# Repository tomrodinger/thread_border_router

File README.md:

# thread_border_router
This is an implementation of a low cost Matter / Thread Border Router to bridge from Ethernet to 802.15.4

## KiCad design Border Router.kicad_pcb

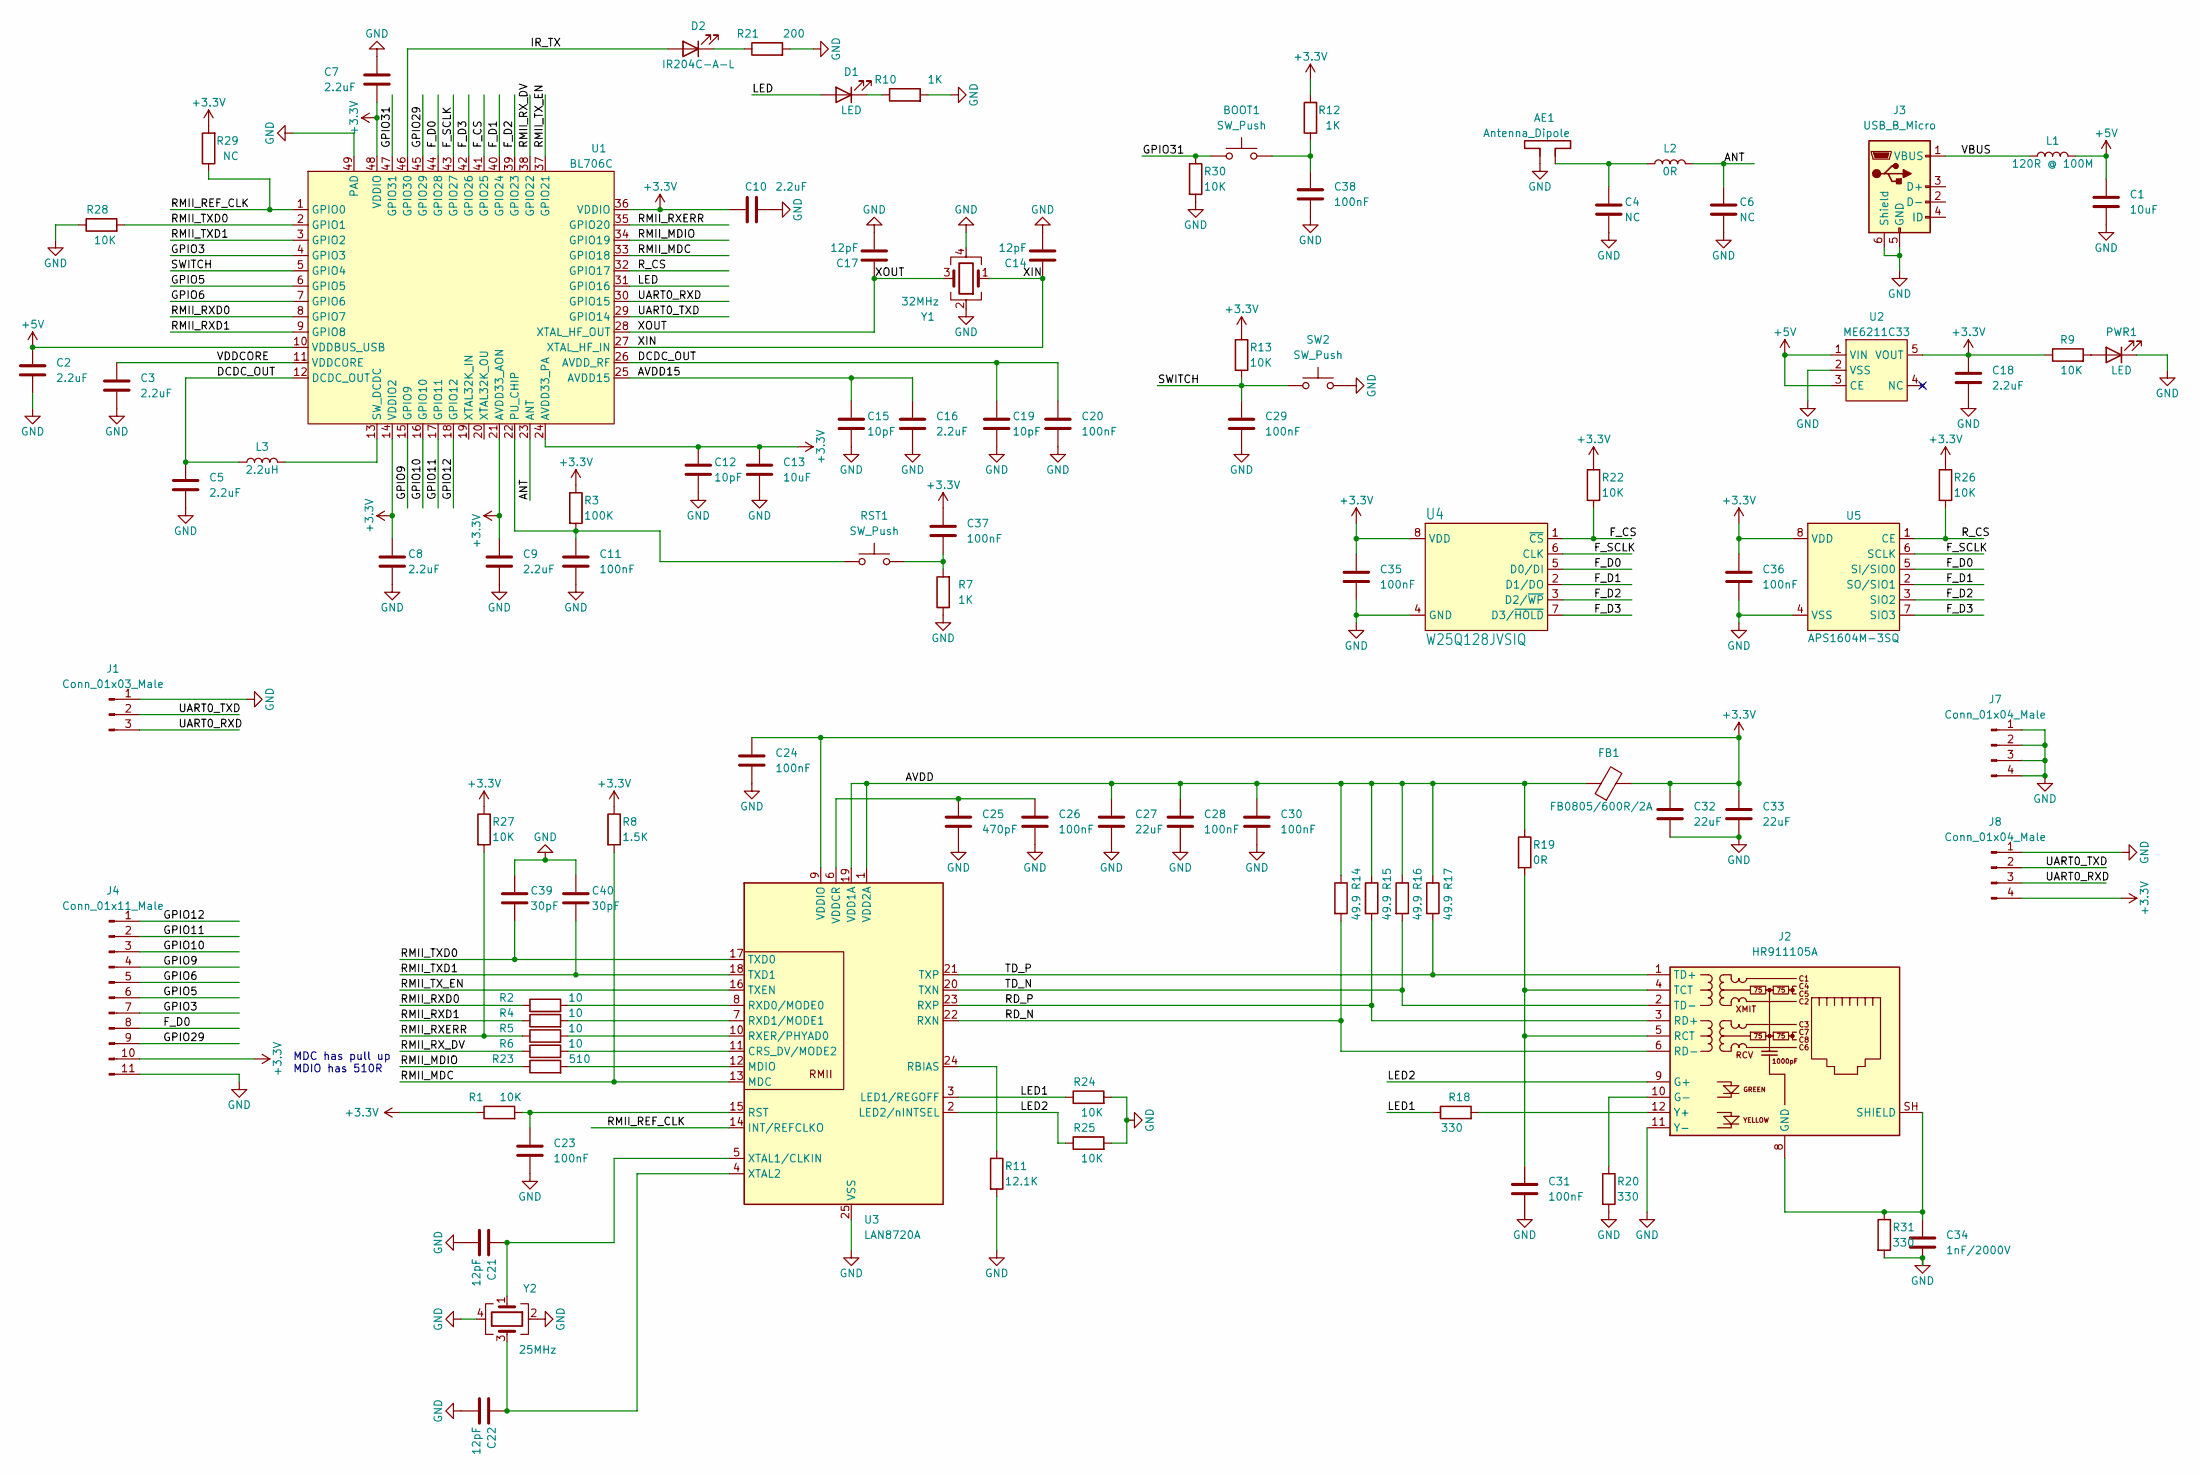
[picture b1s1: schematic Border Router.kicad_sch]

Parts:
AE1: Antenna_Dipole; Texas_SWRA117D_2.4GHz_Right
BOOT1: SW_Push; SW_SPST_EVQPE1; LCSC PN C720477
C1, C13: 10uF; C_0603_1608Metric; LCSC PN C96446
C2, C3, C5, C7, C8, C9, C10, C16, C18: 2.2uF; C_0402_1005Metric; LCSC PN C12530
C4, C6: NC; C_0402_1005Metric
C11, C20, C23, C24, C26, C28, C29, C30, C31, C35, C36, C37, C38: 100nF; C_0402_1005Metric; LCSC PN C307331
C12, C15, C19: 10pF; C_0402_1005Metric; LCSC PN C32949
C14, C21: 12pF; C_0402_1005Metric; LCSC PN C1547
C17, C22: 12pF; C_0402_1005Metric
C25: 470pF; C_0402_1005Metric
C27, C32, C33: 22uF; C_0805_2012Metric
C34: 1nF/2000V; C_1206_3216Metric
C39, C40: 30pF; C_0402_1005Metric
D1: LED; LED_0603_1608Metric; LCSC PN C434420
D2: IR204C-A-L; LED_D3.0mm_Horizontal_O3.81mm_Z2.0mm; LCSC PN C98863
FB1: FB0805/600R/2A; L_0805_2012Metric; LCSC C304329
J1: Conn_01x03_Male; PinHeader_1x03_P2.54mm_Vertical
J2: HR911105A; LCSC C12074
J3: USB_B_Micro; USB_Micro-B_Molex-105017-0001; LCSC C962222
J4: Conn_01x11_Male; PinSocket_1x11_P2.54mm_Vertical
J7, J8: Conn_01x04_Male; PinHeader_1x04_P2.54mm_Vertical
L1: 120R @ 100M; L_0603_1608Metric; LCSC PN C42102
L2: 0R; L_0402_1005Metric
L3: 2.2uH; L_0805_2012Metric; LCSC PN C86089
PWR1: LED; LED_0603_1608Metric; LCSC PN C434420
R1, R9, R13, R22, R24, R25, R26, R27, R28, R30: 10K; R_0402_1005Metric; LCSC PN C25744
R2, R4, R5, R6: 10; R_0402_1005Metric
R3: 100K; R_0402_1005Metric; LCSC PN C25744
R7, R10, R12: 1K; R_0402_1005Metric; LCSC PN C11702
R8: 1.5K; R_0402_1005Metric
R11: 12.1K; R_0402_1005Metric
R14, R15, R16, R17: 49.9; R_0402_1005Metric
R18: 330; R_0402_1005Metric
R19: 0R; R_0402_1005Metric
R20, R31: 330; R_0402_1005Metric; LCSC PN C25123
R21: 200; R_0402_1005Metric
R23: 510; R_0402_1005Metric
R29: NC; R_0402_1005Metric
RST1: SW_Push; SW_SPST_EVQPE1; LCSC PN C720477
SW2: SW_Push; SW_SPST_EVQPE1; LCSC PN C720477
U1: BL706C; QFN-48-1EP_6x6mm_P0.4mm_EP4.3x4.3mm
U2: ME6211C33; SOT-23-5; LCSC PN C82942
U3: LAN8720A; QFN-24-1EP_4x4mm_P0.5mm_EP2.6x2.6mm; LCSC C45223
U4: W25Q128JVSIQ; SOIC-8_5.275x5.275mm_P1.27mm; LCSC C97521
U5: APS1604M-3SQ; SOP-8_3.9x4.9mm_P1.27mm
Y1: 32MHz; Crystal_SMD_2016-4Pin_2.0x1.6mm; LCSC PN C255896
Y2: 25MHz; Crystal_SMD_3225-4Pin_3.2x2.5mm; LCSC PN C9006

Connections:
+3V3: C7.2, C8.1, C9.1, C10.2, C12.1, C13.1, C18.1, C24.1, C32.1, C33.1, C35.1, C36.1, C37.1, FB1.2, J4.10, J8.4, R1.1, R3.1, R8.1, R9.1, R12.2, R13.1, R22.1, R26.1, R27.1, R29.2, U1.14 (VDDIO2), U1.21 (AVDD33_AON), U1.24 (AVDD33_PA), U1.36 (VDDIO), U1.48 (VDDIO), U2.5 (VOUT), U3.9 (VDDIO), U4.8 (VDD), U5.8 (VDD)
+5V: C1.1, C2.1, L1.2, U1.10 (VDDBUS_USB), U2.1 (VIN), U2.3 (CE)
/ANT: C6.1, L2.2, U1.23 (ANT)
/AVDD: C27.1, C28.1, C30.1, FB1.1, R14.1, R15.1, R16.1, R17.1, R19.1, U3.1 (VDD2A), U3.19 (VDD1A)
/AVDD15: C15.1, C16.1, U1.25 (AVDD15)
/DCDC_OUT: C5.1, C19.1, C20.1, L3.1, U1.12 (DCDC_OUT), U1.26 (AVDD_RF)
/F_CS: R22.2, U1.41 (GPIO25), U4.1 (~CS)
/F_D0: J4.8, U1.44 (GPIO28), U4.5 (D0/DI), U5.5 (SI/SIO0)
/F_D1: U1.40 (GPIO24), U4.2 (D1/DO), U5.2 (SO/SIO1)
/F_D2: U1.39 (GPIO23), U4.3 (D2/~WP), U5.3 (SIO2)
/F_D3: U1.42 (GPIO26), U4.7 (D3/~HOLD), U5.7 (SIO3)
/F_SCLK: U1.43 (GPIO27), U4.6 (CLK), U5.6 (SCLK)
/GPIO3: J4.7, U1.4 (GPIO3)
/GPIO5: J4.6, U1.6 (GPIO5)
/GPIO6: J4.5, U1.7 (GPIO6)
/GPIO9: J4.4, U1.15 (GPIO9)
/GPIO10: J4.3, U1.16 (GPIO10)
/GPIO11: J4.2, U1.17 (GPIO11)
/GPIO12: J4.1, U1.18 (GPIO12)
/GPIO29: J4.9, U1.45 (GPIO29)
/GPIO31: BOOT1.1, R30.1, U1.47 (GPIO31)
/IR_TX: D2.2 (A), U1.46 (GPIO30)
/LED: D1.2 (A), U1.31 (GPIO16)
/LED1: R18.1, R24.1, U3.3 (LED1/REGOFF)
/LED2: J2.9 (G+), R25.1, U3.2 (LED2/nINTSEL)
/RD_N: J2.6 (RD-), R14.2, U3.22 (RXN)
/RD_P: J2.3 (RD+), R15.2, U3.23 (RXP)
/RMII_MDC: R8.2, U1.33 (GPIO18), U3.13 (MDC)
/RMII_MDIO: R23.1, U1.34 (GPIO19)
/RMII_REF_CLK: R29.1, U1.1 (GPIO0), U3.14 (INT/REFCLKO)
/RMII_RXD0: R2.1, U1.8 (GPIO7)
/RMII_RXD1: R4.1, U1.9 (GPIO8)
/RMII_RXERR: R5.1, R27.2, U1.35 (GPIO20)
/RMII_RX_DV: R6.1, U1.38 (GPIO22)
/RMII_TXD0: C39.2, R28.2, U1.2 (GPIO1), U3.17 (TXD0)
/RMII_TXD1: C40.2, U1.3 (GPIO2), U3.18 (TXD1)
/RMII_TX_EN: U1.37 (GPIO21), U3.16 (TXEN)
/R_CS: R26.2, U1.32 (GPIO17), U5.1 (CE)
/SWITCH: C29.1, R13.2, SW2.1, U1.5 (GPIO4)
/TD_N: J2.2 (TD-), R16.2, U3.20 (TXN)
/TD_P: J2.1 (TD+), R17.2, U3.21 (TXP)
/UART0_RXD: J1.3, J8.3, U1.30 (GPIO15)
/UART0_TXD: J1.2, J8.2, U1.29 (GPIO14)
/VBUS: J3.1 (VBUS), L1.1
/VDDCORE: C3.1, U1.11 (VDDCORE)
/XIN: C14.1, U1.27 (XTAL_HF_IN), Y1.1
/XOUT: C17.1, U1.28 (XTAL_HF_OUT), Y1.3
GND: AE1.2, C1.2, C2.2, C3.2, C4.2, C5.2, C6.2, C7.1, C8.2, C9.2, C10.1, C11.2, C12.2, C13.2, C14.2, C15.2, C16.2, C17.2, C18.2, C19.2, C20.2, C21.2, C22.2, C23.2, C24.2, C25.2, C26.2, C27.2, C28.2, C29.2, C30.2, C31.2, C32.2, C33.2, C34.2, C35.2, C36.2, C38.2, C39.1, C40.1, J1.1, J2.11 (Y-), J3.5 (GND), J3.6 (Shield), J4.11, J7.1, J7.2, J7.3, J7.4, J8.1, PWR1.1 (K), R7.1, R10.2, R11.2, R20.2, R21.2, R24.2, R25.2, R28.1, R30.2, R31.2, SW2.2, U1.49 (PAD), U2.2 (VSS), U3.25 (VSS), U4.4 (GND), U5.4 (VSS), Y1.2, Y1.4, Y2.2, Y2.4
unnamed: AE1.1, C4.1, L2.1
unnamed: BOOT1.2, C38.1, R12.1
unnamed: C11.1, R3.2, RST1.1, U1.22 (PU_CHIP)
unnamed: C21.1, U3.5 (XTAL1/CLKIN), Y2.1
unnamed: C22.1, U3.4 (XTAL2), Y2.3
unnamed: C23.1, R1.2, U3.15 (RST)
unnamed: C25.1, C26.1, U3.6 (VDDCR)
unnamed: C31.1, J2.4 (TCT), J2.5 (RCT), R19.2
unnamed: C34.1, J2.8 (GND), J2.SH (SHIELD), R31.1
unnamed: C37.2, R7.2, RST1.2
unnamed: D1.1 (K), R10.1
unnamed: D2.1 (K), R21.1
unnamed: J2.10 (G-), R20.1
unnamed: J2.12 (Y+), R18.2
unnamed: L3.2, U1.13 (SW_DCDC)
unnamed: PWR1.2 (A), R9.2
unnamed: R2.2, U3.8 (RXD0/MODE0)
unnamed: R4.2, U3.7 (RXD1/MODE1)
unnamed: R5.2, U3.10 (RXER/PHYAD0)
unnamed: R6.2, U3.11 (CRS_DV/MODE2)
unnamed: R11.1, U3.24 (RBIAS)
unnamed: R23.2, U3.12 (MDIO)

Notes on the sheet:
MDC has pull up MDIO has 510R

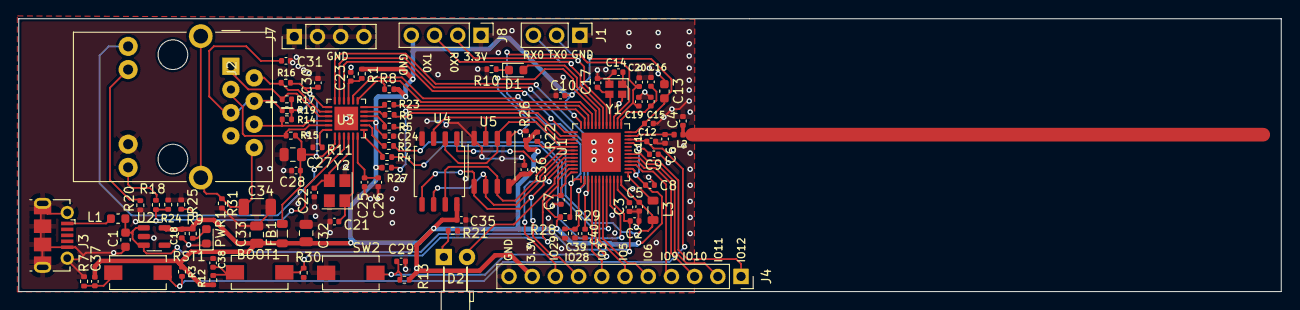
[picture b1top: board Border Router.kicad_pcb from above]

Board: 2 copper layers, 138.2 x 29.9 mm, 94 parts (0 on the bottom side), 70 nets.

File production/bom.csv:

Designator,Footprint,Quantity,Value,LCSC Part #
"BOOT1, RST1, SW2",SW_SPST_EVQPE1,3,SW_Push,
"C1, C13",C_0603_1608Metric,2,10uF,
"C10, C16, C18, C2, C3, C5, C7, C8, C9",C_0402_1005Metric,9,2.2uF,
"C11, C20, C23, C24, C26, C28, C29, C30, C31, C35, C36, C37, C38",C_0402_1005Metric,13,100nF,
"C12, C15, C19",C_0402_1005Metric,3,10pF,
"C14, C17, C21, C22",C_0402_1005Metric,4,12pF,
C25,C_0402_1005Metric,1,470pF,
"C27, C32, C33",C_0805_2012Metric,3,22uF,
C34,C_1206_3216Metric,1,1nF/2000V,
"C39, C40",C_0402_1005Metric,2,30pF,
"C4, C6",C_0402_1005Metric,2,NC,
"D1, PWR1",LED_0603_1608Metric,2,LED,
D2,LED_D3.0mm_Horizontal_O3.81mm_Z2.0mm,1,IR204C-A-L,
FB1,L_0805_2012Metric,1,FB0805/600R/2A,C304329
J1,PinHeader_1x03_P2.54mm_Vertical,1,Conn_01x03_Male,
J2,HR911105A,1,RJ45_Bel_SI-60062-F,C12074
J3,USB_Micro-B_Molex-105017-0001,1,USB_B_Micro,C962222
J4,PinSocket_1x11_P2.54mm_Vertical,1,Conn_01x11_Male,
"J7, J8",PinHeader_1x04_P2.54mm_Vertical,2,Conn_01x04_Male,
L1,L_0603_1608Metric,1,120R @ 100M,
L2,L_0402_1005Metric,1,0R,
L3,L_0805_2012Metric,1,2.2uH,
"R1, R13, R22, R24, R25, R26, R27, R28, R30, R9",R_0402_1005Metric,10,10K,
"R10, R12, R7",R_0402_1005Metric,3,1K,
R11,R_0402_1005Metric,1,12.1K,
"R14, R15, R16, R17",R_0402_1005Metric,4,49.9,
"R18, R20, R31",R_0402_1005Metric,3,330,
R19,R_0402_1005Metric,1,0R,
"R2, R4, R5, R6",R_0402_1005Metric,4,10,
R21,R_0402_1005Metric,1,200,
R23,R_0402_1005Metric,1,510,
R29,R_0402_1005Metric,1,NC,
R3,R_0402_1005Metric,1,100K,
R8,R_0402_1005Metric,1,1.5K,
U1,QFN-48-1EP_6x6mm_P0.4mm_EP4.3x4.3mm,1,BL706C,
U2,SOT-23-5,1,ME6211C33,
U3,QFN-24-1EP_4x4mm_P0.5mm_EP2.6x2.6mm,1,LAN8720A,C45223
U4,SOIC-8_5.275x5.275mm_P1.27mm,1,W25Q128JVSIQ,C97521
U5,SOP-8_3.9x4.9mm_P1.27mm,1,APS1604M-3SQ,
Y1,Crystal_SMD_2016-4Pin_2.0x1.6mm,1,32MHz,
Y2,Crystal_SMD_3225-4Pin_3.2x2.5mm,1,25MHz,

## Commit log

2023-03-02 Border Router
